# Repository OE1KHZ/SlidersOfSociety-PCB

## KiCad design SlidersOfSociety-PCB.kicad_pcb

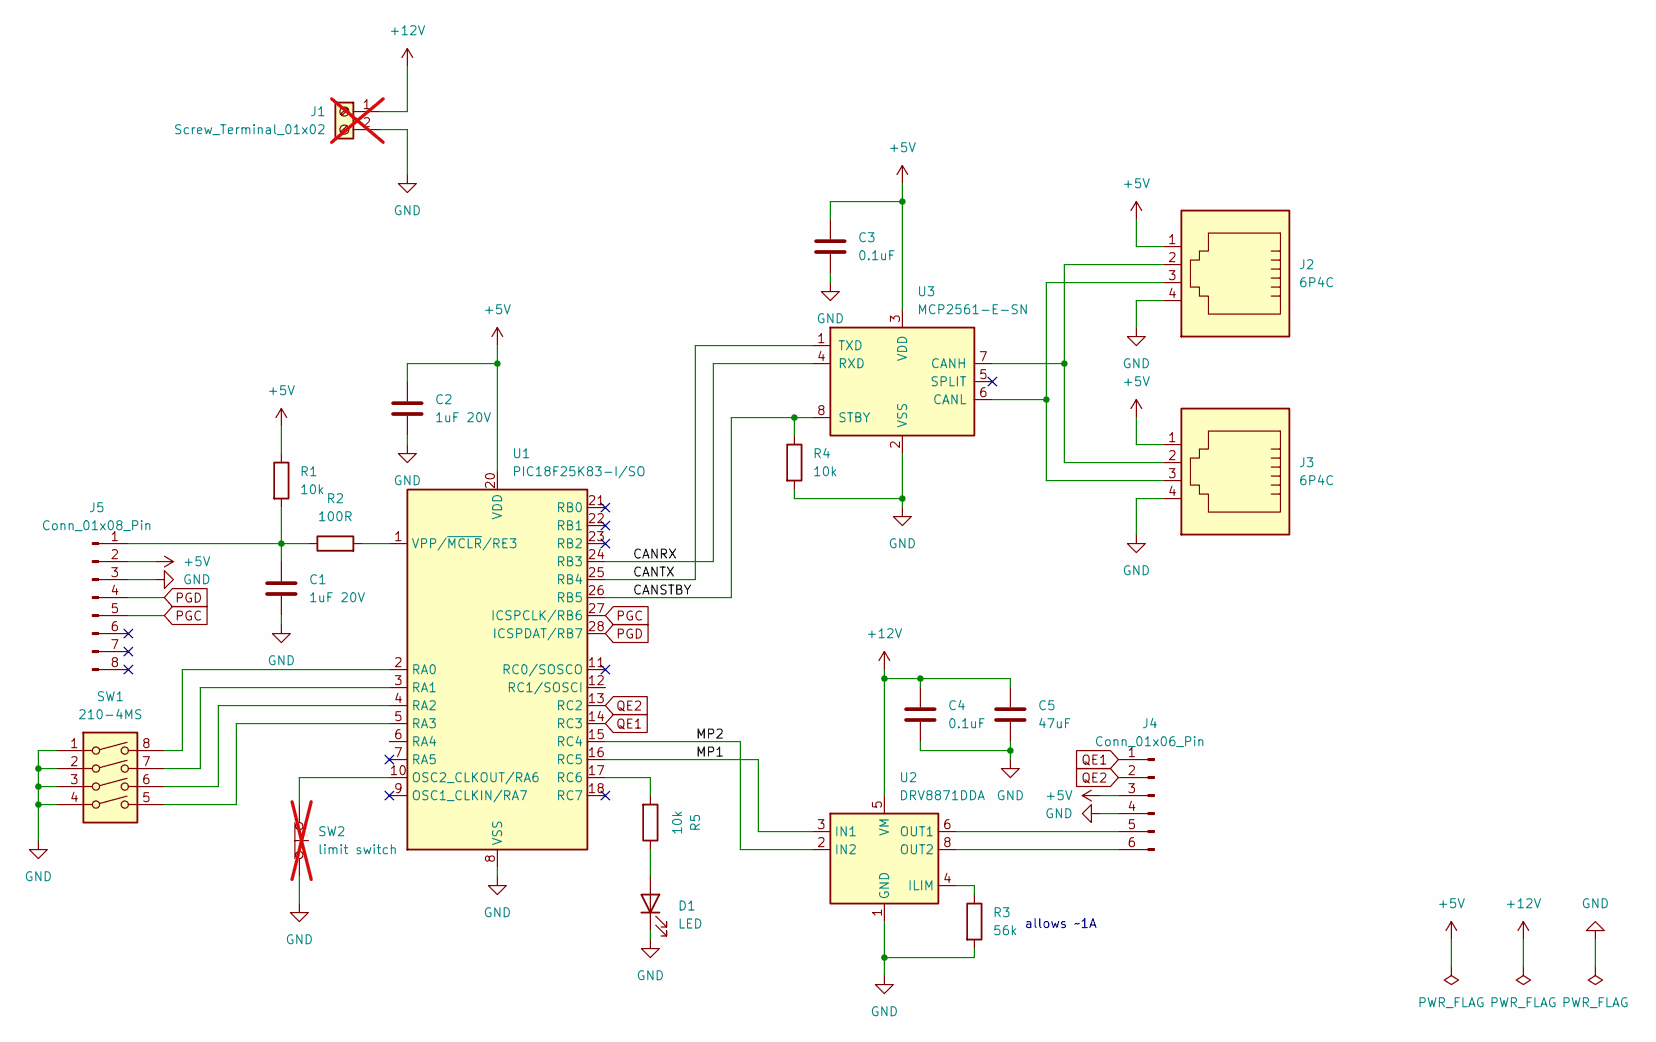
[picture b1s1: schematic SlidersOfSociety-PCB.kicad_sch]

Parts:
C1, C2: 1uF 20V; C_0805_2012Metric_Pad1.18x1.45mm_HandSolder; MPN CL21B105KBFNNNE
C3, C4: 0.1uF; C_0805_2012Metric_Pad1.18x1.45mm_HandSolder; MPN CC0805KRX7R9BB104
C5: 47uF; C_Radial_D10.0mm_H12.5mm_P5.00mm; MPN UHE2A470MPD
D1: LED; LED_D3.0mm; MPN 151031VS06000
J1: Screw_Terminal_01x02; TerminalBlock_MaiXu_MX126-5.0-02P_1x02_P5.00mm; not fitted
J2, J3: 6P4C; RJ14_Connfly_DS1133-S4_Horizontal; MPN MTJ-642BX2
J4: Conn_01x06_Pin; PinHeader_1x06_P2.54mm_Vertical
J5: Conn_01x08_Pin; PinHeader_1x08_P2.54mm_Vertical
R1, R4, R5: 10k; R_0805_2012Metric_Pad1.20x1.40mm_HandSolder; MPN CRCW080510K0FKEA
R2: 100R; R_0805_2012Metric_Pad1.20x1.40mm_HandSolder; MPN RC0805FR-07100RL
R3: 56k; R_0805_2012Metric_Pad1.20x1.40mm_HandSolder; MPN RC0805FR-0756KL
SW1: 210-4MS; SW_DIP_SPSTx04_Slide_6.7x11.72mm_W7.62mm_P2.54mm_LowProfile; MPN 219-4MST
SW2: limit switch; JST_XH_B2B-XH-A_1x02_P2.50mm_Vertical; not fitted
U1: PIC18F25K83-I/SO; SOIC-28W_7.5x18.7mm_P1.27mm; MPN PIC18F25K83-I/SO
U2: DRV8871DDA; Texas_HTSOP-8-1EP_3.9x4.9mm_P1.27mm_EP2.95x4.9mm_Mask2.4x3.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; MPN DRV8871DDAR
U3: MCP2561-E-SN; SOIC-8_3.9x4.9mm_P1.27mm; MPN MCP2561T-E/SN

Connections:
+5V: C2.1, C3.1, J2.1, J3.1, J4.3, J5.2, R1.1, U1.20 (VDD), U3.3 (VDD)
+12V: C4.1, C5.1, J1.1, U2.5 (VM)
/CANRX: U1.24 (RB3), U3.4 (RXD)
/CANSTBY: R4.1, U1.26 (RB5), U3.8 (STBY)
/CANTX: U1.25 (RB4), U3.1 (TXD)
/MP1: U1.16 (RC5), U2.3 (IN1)
/MP2: U1.15 (RC4), U2.2 (IN2)
GND: C1.2, C2.2, C3.2, C4.2, C5.2, D1.1 (K), J1.2, J2.4, J3.4, J4.4, J5.3, R3.2, R4.2, SW1.1, SW1.2, SW1.3, SW1.4, SW2.2 (B), U1.8 (VSS), U1.19 (VSS), U2.1 (GND), U2.7 (GND), U2.9 (GND), U3.2 (VSS)
unnamed: D1.2 (A), R5.1
unnamed: J4.5, U2.6 (OUT1)
unnamed: J4.6, U2.8 (OUT2)
unnamed: C1.1, J5.1, R1.2, R2.1
unnamed: SW2.1 (A), U1.10 (OSC2_CLKOUT/RA6)
unnamed: SW1.8, U1.2 (RA0)
unnamed: SW1.7, U1.3 (RA1)
unnamed: SW1.6, U1.4 (RA2)
unnamed: SW1.5, U1.5 (RA3)
unnamed: R5.2, U1.17 (RC6)
unnamed: R2.2, U1.1 (VPP/~MCLR/RE3)
unnamed: R3.1, U2.4 (ILIM)
unnamed: J2.2, J3.2, U3.7 (CANH)
unnamed: J2.3, J3.3, U3.6 (CANL)
PGC: J5.5, U1.27 (ICSPCLK/RB6)
PGD: J5.4, U1.28 (ICSPDAT/RB7)
QE1: J4.1, U1.14 (RC3)
QE2: J4.2, U1.13 (RC2)

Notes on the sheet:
allows ~1A

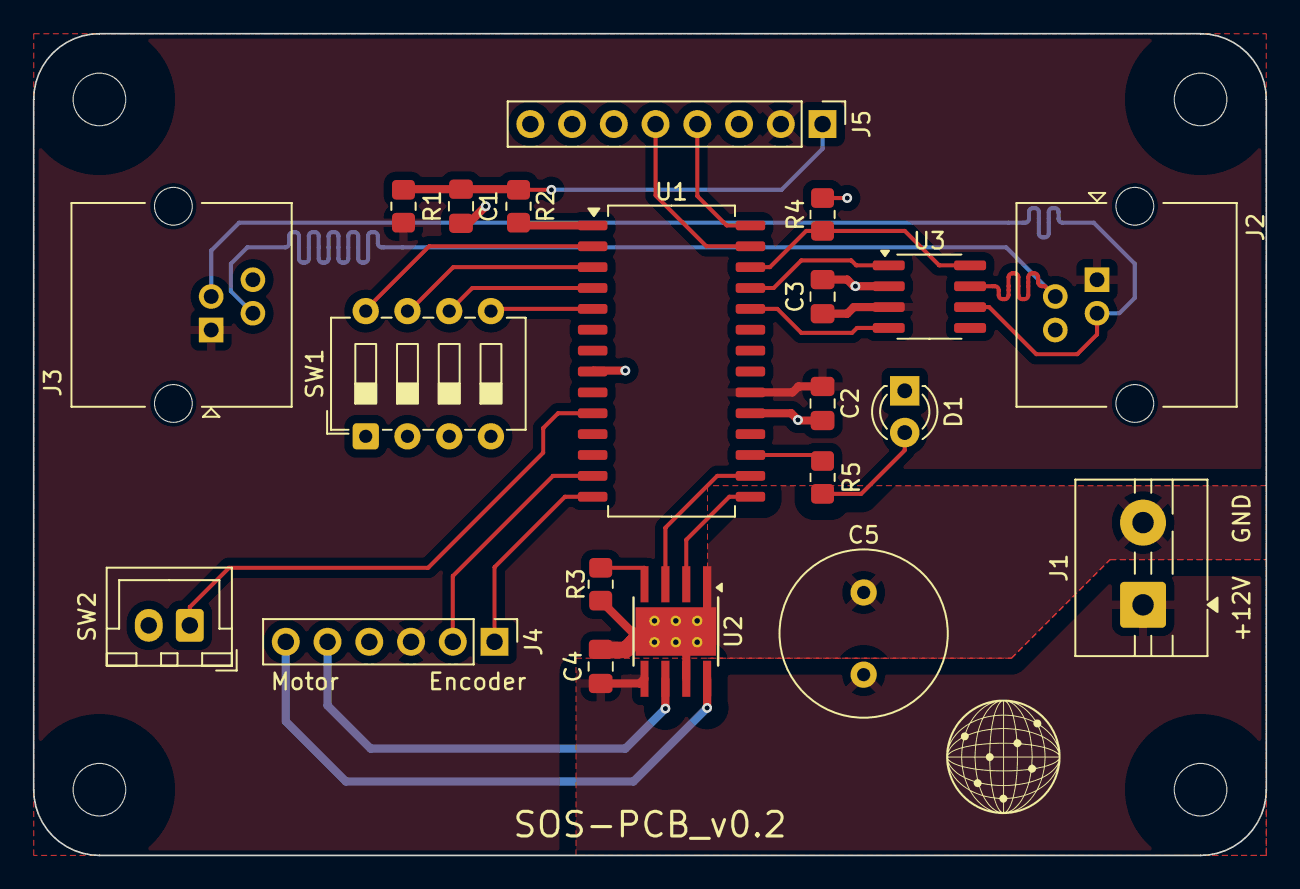
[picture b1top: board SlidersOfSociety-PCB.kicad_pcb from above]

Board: 2 copper layers, 75.0 x 50.0 mm, 21 parts (0 on the bottom side), 26 nets.

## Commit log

2025-07-12 init commit
2025-07-14 bump to kicad 9.0.2
2025-07-16 add custom drc
2025-07-18 finish pcb layout v0.2
2025-07-21 add branding
2025-08-21 idk what changed here, been some time
2025-08-21 add license
